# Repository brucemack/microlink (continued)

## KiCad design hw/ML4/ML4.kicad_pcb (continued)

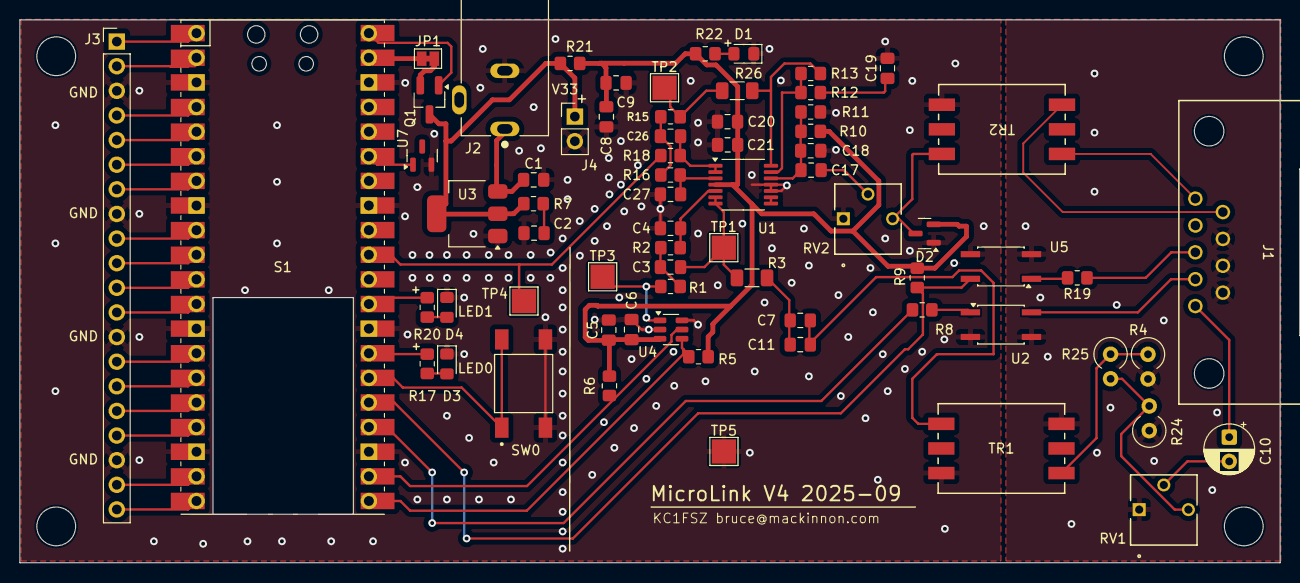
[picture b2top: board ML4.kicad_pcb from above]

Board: 2 copper layers, 130.0 x 56.0 mm, 73 parts (0 on the bottom side), 64 nets.

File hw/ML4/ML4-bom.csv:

"Reference","Value","LCSC","Datasheet","BOM Comments","Footprint","Qty","DNP","DK"
"C1,C2","22u","C45783","~","","Capacitor_SMD:C_0805_2012Metric_Pad1.18x1.45mm_HandSolder","2","",""
"C3,C26","22n","C1729","~","","Capacitor_SMD:C_0805_2012Metric_Pad1.18x1.45mm_HandSolder","2","",""
"C4,C27","10n","C1710 ","~","","Capacitor_SMD:C_0805_2012Metric_Pad1.18x1.45mm_HandSolder","2","",""
"C5,C7,C8,C9,C11,C17,C19,C20","47u","C16780 ","~","","Capacitor_SMD:C_0805_2012Metric_Pad1.18x1.45mm_HandSolder","8","",""
"C6,C18,C21","0.1u","C28233 ","~","","Capacitor_SMD:C_0805_2012Metric_Pad1.18x1.45mm_HandSolder","3","",""
"C10","47u (Optional DC Block)","C22320","~","","Capacitor_THT:CP_Radial_D5.0mm_P2.50mm","1","",""
"D2","BAT54S","C12765","https://www.diodes.com/assets/Datasheets/ds11005.pdf","","Package_TO_SOT_SMD:SOT-23","1","",""
"J1","DE9_Receptacle","C17515865","~","","bruce-footprints:CONN_A-DF 09 A&slash_KG-T2S_ASM","1","","AE10921-ND"
"J2","PJ-102AH","C3096093","","","bruce-footprints:Power_5.5mm_CUI_PJ-102AH","1","","CP-102AH-ND"
"J3","Conn_01x20","C22465880","~","Standard 2.54mm pin header","Connector_PinHeader_2.54mm:PinHeader_1x20_P2.54mm_Vertical","1","",""
"J4","Conn_01x02","C492401","~","Standard 2.54mm pin header","Connector_PinHeader_2.54mm:PinHeader_1x02_P2.54mm_Vertical","1","",""
"Q1","DMG2305UX-13","C144153","https://www.diodes.com/assets/Datasheets/DMG2305UX.pdf","","Package_TO_SOT_SMD:SOT-23_Handsoldering","1","",""
"R1,R15","1.5k","C4310","~","","Resistor_SMD:R_0805_2012Metric_Pad1.20x1.40mm_HandSolder","2","",""
"R2,R16","2.7k","C17530","~","","Resistor_SMD:R_0805_2012Metric_Pad1.20x1.40mm_HandSolder","2","",""
"R3,R18","0R","C17477","~","","Resistor_SMD:R_0805_2012Metric_Pad1.20x1.40mm_HandSolder,Resistor_SMD:R_1206_3216Metric_Pad1.30x1.75mm_HandSolder","2","",""
"R4","620","C58633","~","","Resistor_THT:R_Axial_DIN0309_L9.0mm_D3.2mm_P2.54mm_Vertical","1","",""
"R5,R6,R12,R13","2.2k","C17520","~","","Resistor_SMD:R_0805_2012Metric_Pad1.20x1.40mm_HandSolder","4","",""
"R7","10","C17415","~","","Resistor_SMD:R_0805_2012Metric_Pad1.20x1.40mm_HandSolder","1","",""
"R8,R19","220","C17557","~","","Resistor_SMD:R_0805_2012Metric_Pad1.20x1.40mm_HandSolder","2","",""
"R9","1k","C17513","~","","Resistor_SMD:R_0805_2012Metric_Pad1.20x1.40mm_HandSolder","1","",""
"R10","330k 1%","C17629","~","","Resistor_SMD:R_0805_2012Metric_Pad1.20x1.40mm_HandSolder","1","",""
"R11","270k 1%","C17589","~","","Resistor_SMD:R_0805_2012Metric_Pad1.20x1.40mm_HandSolder","1","",""
"R17,R20,R22","100","C17408","~","","Resistor_SMD:R_0805_2012Metric_Pad1.20x1.40mm_HandSolder","3","",""
"R21","4.7","C17675","~","","Resistor_SMD:R_0805_2012Metric_Pad1.20x1.40mm_HandSolder","1","",""
"R24","2,.2k","C58595 ","~","","Resistor_THT:R_Axial_DIN0309_L9.0mm_D3.2mm_P2.54mm_Vertical","1","",""
"R25","39k","C58645","~","","Resistor_THT:R_Axial_DIN0309_L9.0mm_D3.2mm_P2.54mm_Vertical","1","",""
"R26","0R 1206","C17888","~","","Resistor_SMD:R_1206_3216Metric_Pad1.30x1.75mm_HandSolder","1","",""
"RV1,RV2","50k","C81264","~","","bruce-footprints:POT_3362P","2","",""
"S1","~","C7203003","","","bruce-footprints:RPi_PicoW_SMD_TH","1","",""
"SW0","TS04-66-55-BK-160-SMT","C4364775","","","bruce-footprints:SW_TS04-66-55-BK-160-SMT","1","",""
"TR1,TR2","SM-LP-5001","C7503474","https://www.bourns.com/docs/Product-Datasheets/SMLP5001.pdf","","bruce-footprints:TRAN6_SM-LP-5001_BRN","2","",""
"U1","TLV9164PWR","C4368361","http://www.ti.com/lit/ds/symlink/lmv324.pdf","","Package_SO:TSSOP-14_4.4x5mm_P0.65mm","1","",""
"U2,U5","LTV-356T","C125117 ","http://optoelectronics.liteon.com/upload/download/DS70-2001-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","","Package_SO:SO-4_4.4x3.6mm_P2.54mm","2","",""
"U3","LM1117MP-3.3","C9662","http://www.ti.com/lit/ds/symlink/lm1117.pdf","","Package_TO_SOT_SMD:SOT-223-3_TabPin2","1","",""
"U4","MCP4725A0T-E/CH","C144198","http://ww1.microchip.com/downloads/en/DeviceDoc/22039d.pdf","","Package_TO_SOT_SMD:SOT-23-6","1","",""
"U7","LM4040D30IDBZR","C2157213","http://www.ti.com/lit/ds/symlink/lm4040-n.pdf","","Package_TO_SOT_SMD:SOT-23","1","",""
"D1","Red","C84256","~","","LED_SMD:LED_0805_2012Metric_Pad1.15x1.40mm_HandSolder","1","",""
"D3","Blue","C84259 ","~","","LED_SMD:LED_0805_2012Metric_Pad1.15x1.40mm_HandSolder","1","",""
"D4","Green","C2297","~","","LED_SMD:LED_0805_2012Metric_Pad1.15x1.40mm_HandSolder","1","",""

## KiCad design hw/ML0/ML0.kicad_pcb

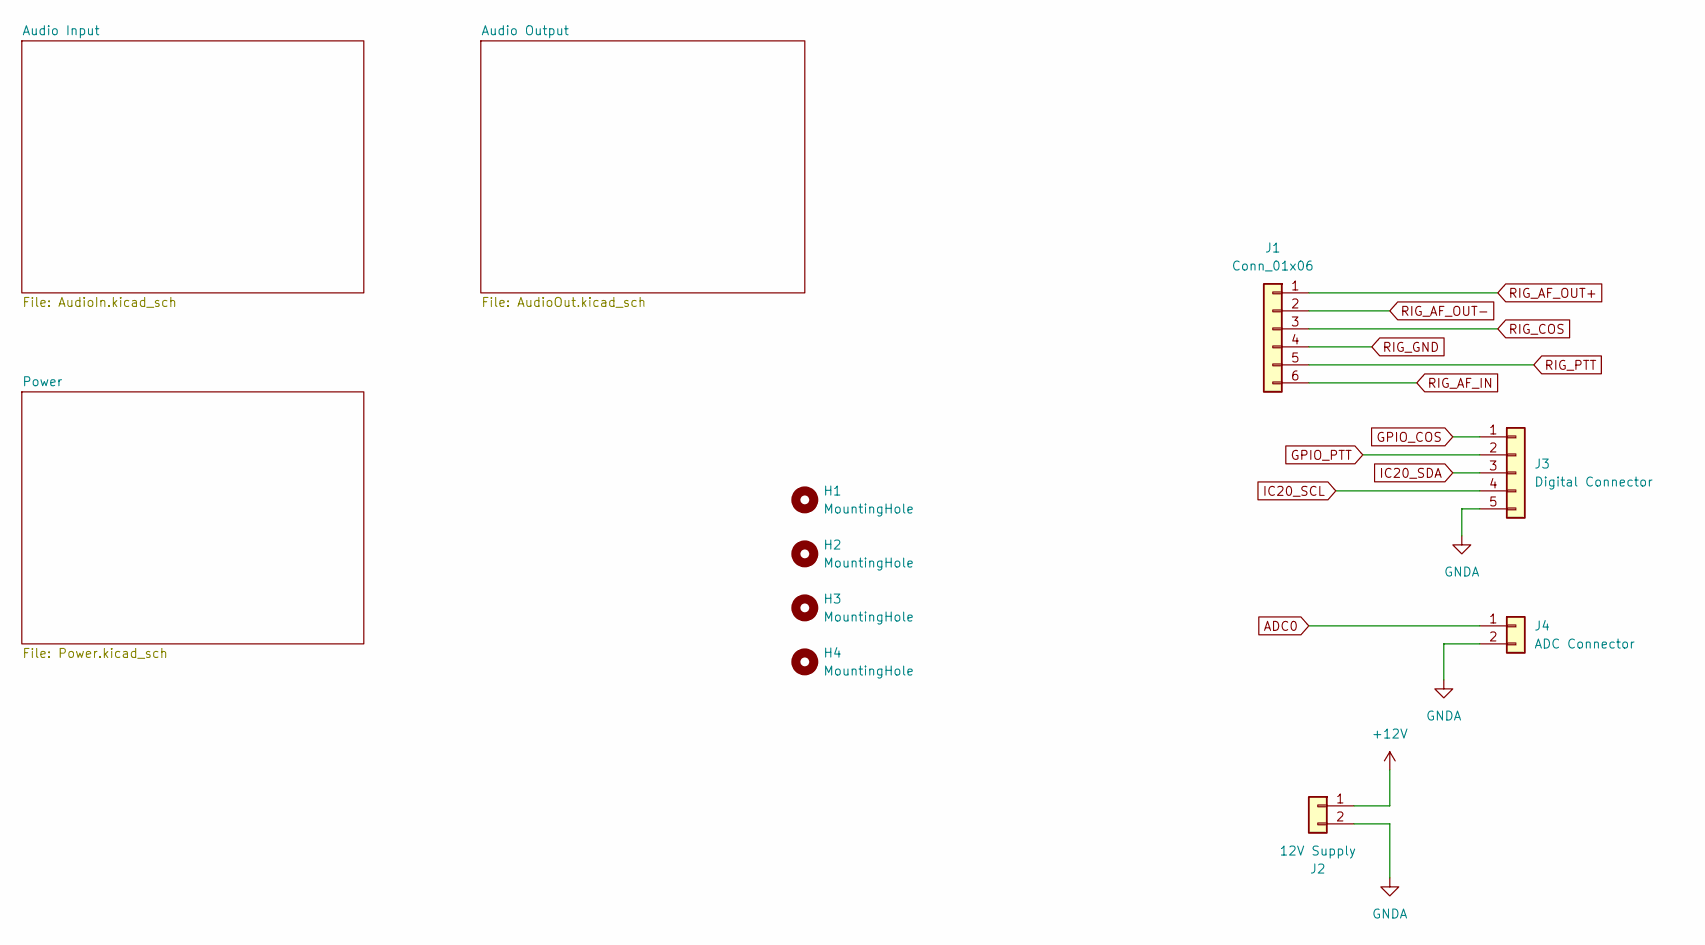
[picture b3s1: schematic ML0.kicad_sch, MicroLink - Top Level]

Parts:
H1, H2, H3, H4: MountingHole; MountingHole_4mm
J1: Conn_01x06; PinHeader_1x06_P2.54mm_Vertical
J2: 12V Supply; PinHeader_1x02_P2.54mm_Vertical
J3: Digital Connector; PinHeader_1x05_P2.54mm_Vertical
J4: ADC Connector; PinHeader_1x02_P2.54mm_Vertical

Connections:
+12V: J2.1; also elsewhere on the board
ADC0: J4.1; also elsewhere on the board
GNDA: J2.2, J3.5, J4.2; also elsewhere on the board
GPIO_COS: J3.1; also elsewhere on the board
GPIO_PTT: J3.2; also elsewhere on the board
IC20_SCL: J3.4; also elsewhere on the board
IC20_SDA: J3.3; also elsewhere on the board
RIG_AF_IN: J1.6; also elsewhere on the board
RIG_AF_OUT+: J1.1; also elsewhere on the board
RIG_AF_OUT-: J1.2; also elsewhere on the board
RIG_COS: J1.3; also elsewhere on the board
RIG_GND: J1.4; also elsewhere on the board
RIG_PTT: J1.5; also elsewhere on the board

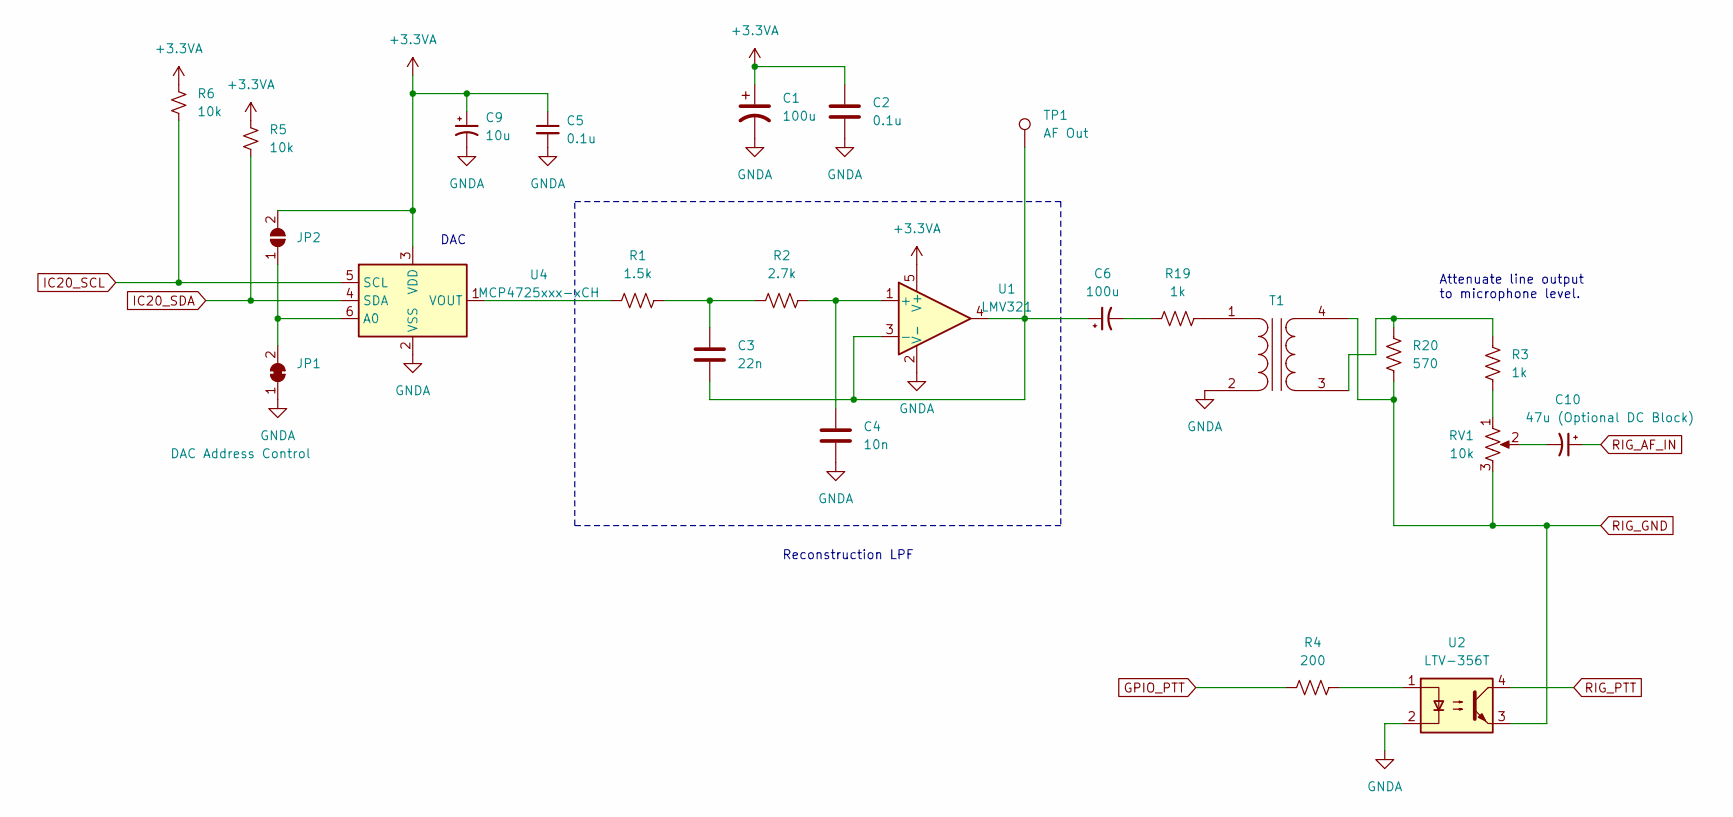
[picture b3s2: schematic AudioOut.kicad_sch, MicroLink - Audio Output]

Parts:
C1, C6: 100u; CAP_KEMET_530_530
C2, C5: 0.1u; C_0805_2012Metric_Pad1.18x1.45mm_HandSolder
C3: 22n; C_0805_2012Metric_Pad1.18x1.45mm_HandSolder
C4: 10n; C_0805_2012Metric_Pad1.18x1.45mm_HandSolder
C9: 10u; CAP_KEMET_530_530
C10: 47u (Optional DC Block); CP_Radial_D5.0mm_P2.50mm
JP1: DAC Address Control; SolderJumper-2_P1.3mm_Bridged_Pad1.0x1.5mm
JP2: SolderJumper_2_Open; SolderJumper-2_P1.3mm_Open_Pad1.0x1.5mm
R1: 1.5k; R_0805_2012Metric_Pad1.20x1.40mm_HandSolder
R2: 2.7k; R_0805_2012Metric_Pad1.20x1.40mm_HandSolder
R3, R19: 1k; R_0805_2012Metric_Pad1.20x1.40mm_HandSolder
R4: 200; R_0805_2012Metric_Pad1.20x1.40mm_HandSolder
R5, R6: 10k; R_0805_2012Metric_Pad1.20x1.40mm_HandSolder
R20: 570; R_0805_2012Metric_Pad1.20x1.40mm_HandSolder
RV1: 10k; POT_3362P
T1: Transformer_1P_1S; CheapAudioTransformer
TP1: AF Out; TestPoint_Pad_2.5x2.5mm
U1: LMV321; SOT-23-5_HandSoldering
U2: LTV-356T; SO-4_4.4x3.6mm_P2.54mm
U4: MCP4725xxx-xCH; SOT-23-6

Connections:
+3.3VA: C1.1, C2.1, C5.1, C9.1, JP2.2 (B), R5.1, R6.1, U1.5 (V+), U4.3 (VDD); also elsewhere on the board
GNDA: C1.2, C2.2, C4.2, C5.2, C9.2, JP1.1 (A), T1.2 (AB), U1.2 (V-), U2.2, U4.2 (VSS); also elsewhere on the board
GPIO_PTT: R4.1; also elsewhere on the board
IC20_SCL: R6.2, U4.5 (SCL); also elsewhere on the board
IC20_SDA: R5.2, U4.4 (SDA); also elsewhere on the board
unnamed: C3.1, R1.1, R2.1
unnamed: C6.2, R19.1
unnamed: C10.2, RV1.2
unnamed: JP1.2 (B), JP2.1 (A), U4.6 (A0)
unnamed: R3.2, RV1.1
unnamed: R4.2, U2.1
unnamed: R19.2, T1.1 (AA)
unnamed: R3.1, R20.1, T1.3 (SA)
unnamed: C4.1, R2.2, U1.1 (+)
unnamed: C3.2, C6.1, TP1.1, U1.3 (-), U1.4
unnamed: R1.2, U4.1 (VOUT)
RIG_AF_IN: C10.1; also elsewhere on the board
RIG_GND: R20.2, RV1.3, T1.4 (SB), U2.3; also elsewhere on the board
RIG_PTT: U2.4; also elsewhere on the board

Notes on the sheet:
Reconstruction LPF
Attenuate line output to microphone level.
DAC

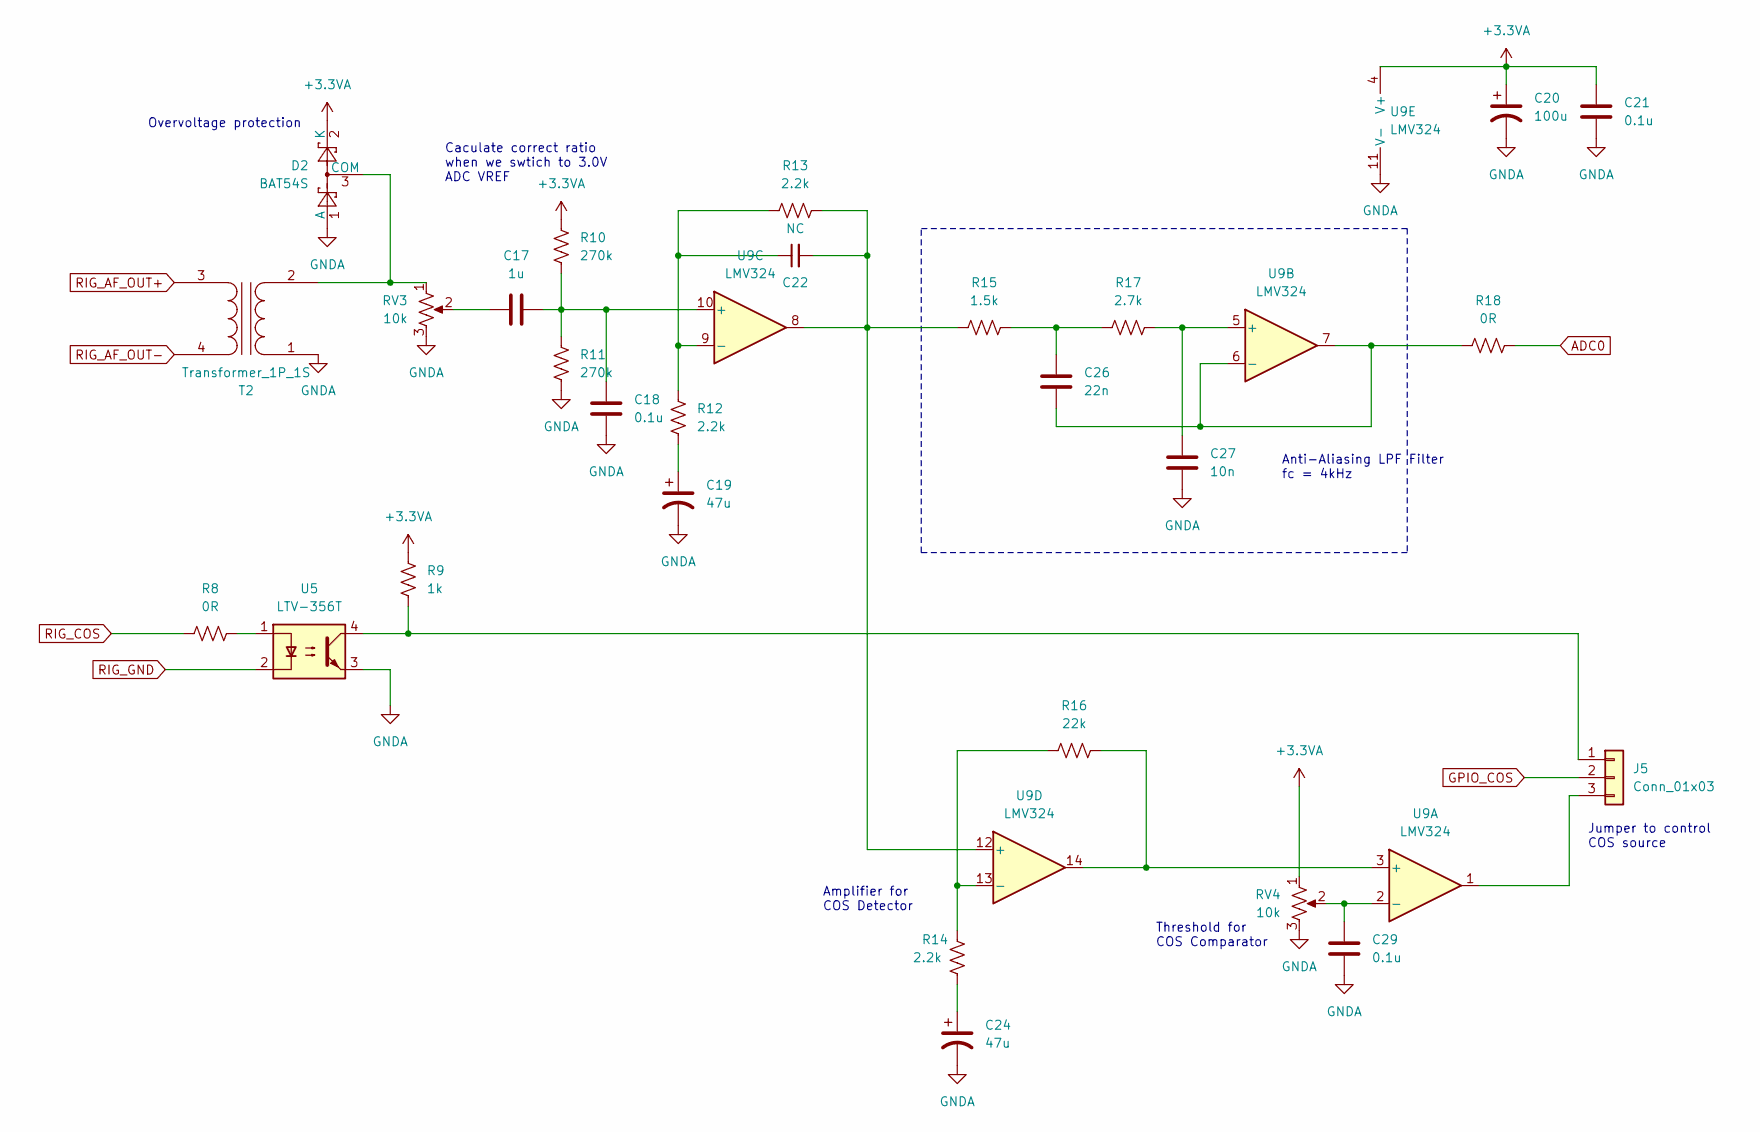
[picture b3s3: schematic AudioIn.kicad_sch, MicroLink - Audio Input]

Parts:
C17: 1u; C_0805_2012Metric_Pad1.18x1.45mm_HandSolder
C18, C21, C29: 0.1u; C_0805_2012Metric_Pad1.18x1.45mm_HandSolder
C19, C24: 47u; CAP_KEMET_530_530
C20: 100u; CAP_KEMET_530_530
C22: NC; C_0805_2012Metric_Pad1.18x1.45mm_HandSolder
C26: 22n; C_0805_2012Metric_Pad1.18x1.45mm_HandSolder
C27: 10n; C_0805_2012Metric_Pad1.18x1.45mm_HandSolder
D2: BAT54S; SOT-23
J5: Conn_01x03; PinHeader_1x03_P2.54mm_Vertical
R8, R18: 0R; R_0805_2012Metric_Pad1.20x1.40mm_HandSolder
R9: 1k; R_0805_2012Metric_Pad1.20x1.40mm_HandSolder
R10, R11: 270k; R_0805_2012Metric_Pad1.20x1.40mm_HandSolder
R12, R13, R14: 2.2k; R_0805_2012Metric_Pad1.20x1.40mm_HandSolder
R15: 1.5k; R_0805_2012Metric_Pad1.20x1.40mm_HandSolder
R16: 22k; R_0805_2012Metric_Pad1.20x1.40mm_HandSolder
R17: 2.7k; R_0805_2012Metric_Pad1.20x1.40mm_HandSolder
RV3, RV4: 10k; POT_3362P
T2: Transformer_1P_1S; CheapAudioTransformer
U5: LTV-356T; SO-4_4.4x3.6mm_P2.54mm
U9: LMV324; TSSOP-14_4.4x5mm_P0.65mm

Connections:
+3.3VA: C20.1, C21.1, D2.2 (K), R9.1, R10.1, RV4.1, U9.4 (V+); also elsewhere on the board
ADC0: R18.2; also elsewhere on the board
GNDA: C18.2, C19.2, C20.2, C21.2, C24.2, C27.2, C29.2, D2.1 (A), R11.2, RV3.3, RV4.3, T2.1 (AA), U5.3, U9.11 (V-); also elsewhere on the board
GPIO_COS: J5.2; also elsewhere on the board
unnamed: C17.1, RV3.2
unnamed: C19.1, R12.1
unnamed: C24.1, R14.1
unnamed: C26.1, R15.1, R17.1
unnamed: D2.3 (COM), RV3.1, T2.2 (AB)
unnamed: J5.1, R9.2, U5.4
unnamed: J5.3, U9.1
unnamed: R8.2, U5.1
unnamed: R16.2, U9.3 (+), U9.14
unnamed: C29.1, RV4.2, U9.2 (-)
unnamed: C27.1, R17.2, U9.5 (+)
unnamed: C26.2, R18.1, U9.6 (-), U9.7
unnamed: C17.2, C18.1, R10.2, R11.1, U9.10 (+)
unnamed: C22.1, R12.2, R13.1, U9.9 (-)
unnamed: C22.2, R13.2, R15.2, U9.8, U9.12 (+)
unnamed: R14.2, R16.1, U9.13 (-)
RIG_AF_OUT+: T2.3 (SA); also elsewhere on the board
RIG_AF_OUT-: T2.4 (SB); also elsewhere on the board
RIG_COS: R8.1; also elsewhere on the board
RIG_GND: U5.2; also elsewhere on the board

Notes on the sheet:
Overvoltage protection
Amplifier for COS Detector
Threshold for COS Comparator
Jumper to control COS source
Anti-Aliasing LPF Filter fc = 4kHz
Caculate correct ratio when we swtich to 3.0V ADC VREF

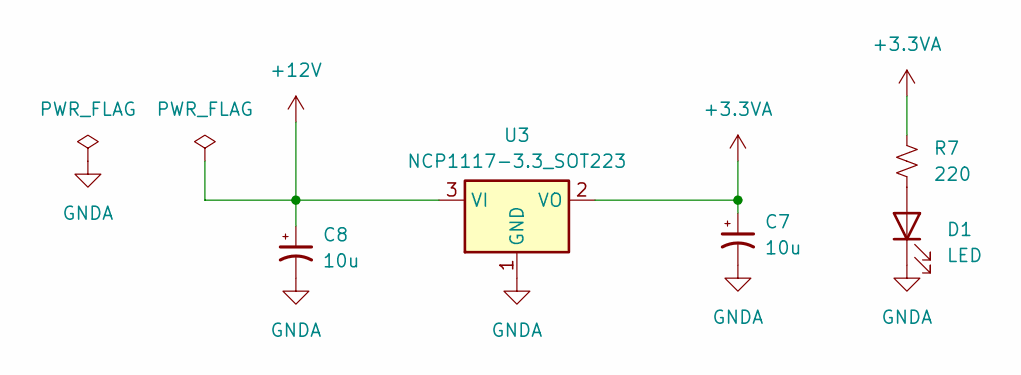
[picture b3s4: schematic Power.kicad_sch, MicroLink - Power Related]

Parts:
C7, C8: 10u; CAP_KEMET_530_530
D1: LED; LED_0805_2012Metric_Pad1.15x1.40mm_HandSolder
R7: 220; R_0805_2012Metric_Pad1.20x1.40mm_HandSolder
U3: NCP1117-3.3_SOT223; SOT-223-3_TabPin2

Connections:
+3.3VA: C7.1, R7.1, U3.2 (VO); also elsewhere on the board
+12V: C8.1, U3.3 (VI); also elsewhere on the board
GNDA: C7.2, C8.2, D1.1 (K), U3.1 (GND); also elsewhere on the board
unnamed: D1.2 (A), R7.2

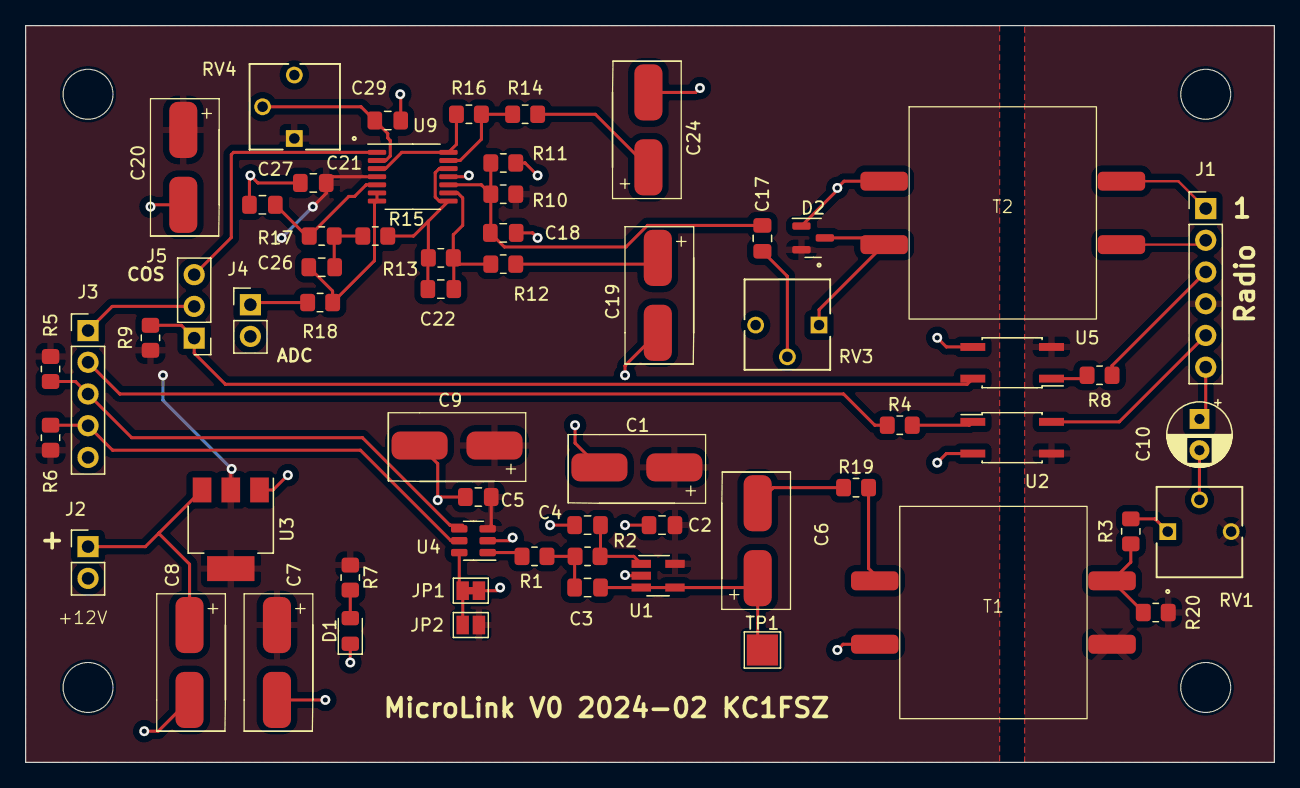
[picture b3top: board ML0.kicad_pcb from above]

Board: 2 copper layers, 100.0 x 59.0 mm, 65 parts (0 on the bottom side), 42 nets.

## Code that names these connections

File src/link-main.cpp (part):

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// ===============

// Phy Pin 21: I2C channel 0 - DAC data
#define I2C0_SDA (16) 
// Phy Pin 22: I2C channel 0 - DAC clock
#define I2C0_SCL (17) 

// Physical pin 23 - GROUND

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#define RIG_KEY_PIN (18)
// Physical pin 25. This is an input (active high) used to detect
// receive carrier from the rig. 
#define RIG_COS_PIN (19)

// No physical pin on board
//#define LED_PIN (25)
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    gpio_set_dir(PTT_PIN, GPIO_IN);
    gpio_pull_up(PTT_PIN);

    gpio_init(RIG_COS_PIN);
    gpio_set_dir(RIG_COS_PIN, GPIO_IN);
    gpio_pull_up(RIG_COS_PIN);

    // Key/indicator LED
    gpio_init(KEY_LED_PIN);
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
    // Setup I2C
    i2c_init(i2c_default, 100 * 1000);
    gpio_set_function(I2C0_SDA, GPIO_FUNC_I2C);
    gpio_set_function(I2C0_SCL, GPIO_FUNC_I2C);
    gpio_pull_up(I2C0_SDA);
    gpio_pull_up(I2C0_SCL);
    //i2c_set_baudrate(i2c_default, 400000 * 4);
    i2c_set_baudrate(i2c_default, 800000);

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        // 2. Soft COS: thresholding noise level on receiver

        bool rigCos = (useHardCos) ? 
            gpio_get(RIG_COS_PIN) : (rxAnalyzer.getRMS() - baselineRxNoise) > (int16_t)rxNoiseThreshold;

        // Produce a debounced cosState, whcih indicates the state of
        // the carrier detect.
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
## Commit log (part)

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2024-01-25 Added example of ONLINE packet
2024-01-25 Centralized the version ID
2024-01-25 Working on directory request
2024-01-25 Server lookup
2024-01-26 Asterisk reference
2024-01-26 Testing on PICO
2024-01-26 Working on cross-platform
2024-01-26 State machine work in process
2024-01-28 Updates from server test
2024-01-28 Cleaned typos
2024-01-28 Working on state machine
2024-01-28 Added more message types
2024-01-28 State machine work
2024-01-28 State machine is working
2024-01-29 Working on socket context
2024-01-29 SocketContext is starting to work, new client test
2024-01-29 Logon/Lookup is working properly on the real EchoLink
2024-01-29 Corrected directory errors
2024-01-29 Switched to NL order on IP address
2024-01-29 UDP working in SocketContext
2024-01-29 Cleaned up oNDATA problem
2024-01-30 Working on audio chain
2024-01-30 W32AudioOutputContext working
2024-01-30 Full receive station working with ECHOTEST
2024-01-30 Cleaned up some test cases
2024-01-30 Refactoring modules
2024-01-30 Cleaning up structure
2024-01-30 Refactoring tools repo
2024-01-30 Moving common files
2024-01-31 Receive test on *ECHOTEST* is working!
2024-01-31 Added some ESP32 stuff
2024-01-31 Working on audio glitch
2024-01-31 Added test case for talking to ESP32 AT commands
2024-02-01 Timing work
2024-02-01 Debugging interupt problems
2024-02-01 Refactored and move things to tools
2024-02-01 Refactoring AT code
2024-02-03 Making improvements to the ATProcessor - more async
2024-02-03 Streamlined AT matcher
2024-02-03 Addressed some AT parsing problems
2024-02-03 added #,CONNECT
2024-02-03 Added support for +CIPDOMAIN
2024-02-03 Starting to integrate EventProcesspr
2024-02-03 Updated state machine
2024-02-03 Working on PI-based EL client
2024-02-04 Initial connection test
2024-02-05 Working on directory lookup
2024-02-05 New lookup working (Verify mode)
2024-02-05 Added information about Extended Verify from K1RFD
2024-02-05 client test 2p
2024-02-05 Connect working!
2024-02-06 Working on initial reset
2024-02-06 Able to maintain sustained QSO with *ECHOTEST*
2024-02-07 Receive audio path is working
2024-02-07 EL receiver is working
2024-02-07 Added jitter-elimination
2024-02-07 Documentation
2024-02-07 Docs
2024-02-07 Cleaning up test cases
2024-02-07 Added information on pacing
2024-02-07 Adding input audio
2024-02-08 Refactoring QSOFlowMachine to support TX (NOT TESTED)
2024-02-08 Refactored SocketContext for Windows, now working on Windows (ECHOTEST)
2024-02-08 Heard an initial test tone back from ECHOTEST, but not fully working
2024-02-08 TX working consistently
2024-02-08 Able to TX a tone and hear it back on *ECHOTEST*
2024-02-08 Adding microphone hardward
2024-02-08 Working on microphone integration
2024-02-08 Seeing ADC queue add fails
2024-02-09 Refactor of ADC code (not tested yet)
2024-02-09 Tone TX working well now
2024-02-09 Successful test with TX and TX!
2024-02-11 Working on fixing deadlock in UART TX path - NOT TESTED
2024-02-11 New TX method tested successfully
2024-02-11 New tone scheme
2024-02-12 Refactoring to include Runnable interface, added timing stuff
2024-02-12 Now enabling ADC for TX only, tested
2024-02-12 Added beep on unsquelch
2024-02-12 Added ability to close a QSO cleanly
2024-02-12 Added model for preamp
2024-02-12 Working on remote linking test case - able to accept UDP traffic
2024-02-13 Added references
2024-02-13 Centering audio on silence
2024-02-13 Schematic updates
2024-02-13 Created test sdes file
2024-02-13 Fixed SDES bug - not tested
2024-02-13 SDES parsing test
2024-02-13 Link station work
2024-02-14 Successful test of W1TKZ-L
2024-02-14 Merged
2024-02-14 Doc improvements
2024-02-14 Removed lock on RX path
2024-02-15 Over the air testing is working
2024-02-16 Working on completing the state machine for linking (NOT TESTED)
2024-02-17 Added BYE support (Not Tested)
2024-02-17 Added timeout for long transmissions, now ignoring inbound traffic from non-accepted peers
2024-02-18 Working on PCB layout
2024-02-18 Link station test passed (on air)!
2024-02-19 Working on voice prompts
2024-02-19 Updating handling of silence
2024-02-19 Prompts working better
2024-02-19 Lowered volume on prompts
2024-02-19 This version of the code had a live QSO with W1DAN and WA1UMU on the WAES repeater.
2024-02-19 Corrected a defect which caused timeout during long TX
2024-02-19 Working on DAC timing
2024-02-20 Docs update
2024-02-20 Working on V0 of the analog PCB
2024-02-20 Adding description of challenge/response login
2024-02-20 Added docs on Login
2024-02-20 Making an offcial station main
2024-02-20 Cleaned up build
2024-02-20 Working on PCB 0
2024-02-21 Updates to docs
2024-02-21 Refactored RX path to enable DTMF in the future. Skipping Welcome after recent activity
2024-02-22 Adding TX audio
2024-02-23 Working on improvements to the audio out
2024-02-24 Refactored _state management. Changed audio output to be driven by ADC clock. (NOT TESTED)
2024-02-24 Working on new DAC scheme
2024-02-24 Now using analytical tone generation instead of lookup table
2024-02-25 Added audio analyzer on TX
2024-02-25 Initial layout done
2024-02-25 Working on PCB
2024-02-26 Improvements to board
2024-02-26 Board sent to JLC on 2024-02-26 09:18 EST
2024-02-26 DTMF detector is working
2024-02-27 Working on debug of audio glitches
2024-02-27 Moved configuration information into flash - no more hard-coding callsign/password
2024-02-27 Improved logging
2024-02-27 Improving logging
2024-02-27 Integrated serial log for OpenLog hardware
2024-02-27 Serial logging working now
2024-02-28 Working on DTMF
2024-02-29 Improved COS handling
2024-02-29 First board
2024-02-29 DTMF test case workig
2024-02-29 DTMF test passing (mostly)
2024-03-04 Working on Pico W integration
2024-03-05 Removed panic, added assignment operator to Channel
2024-03-05 Tested successfully on Pico W
2024-03-05 Working on multi-user conference (not tested)
2024-03-06 Preliminary push of conference-enabled link (NOT TESTED)
2024-03-06 LogonMachine2 is working
2024-03-06 ConferenceBridge added
2024-03-06 Conference authorization is working
2024-03-06 ECHOTEST successful via conference
2024-03-06 Physical radio TX path tested
2024-03-07 Full system (w/ radio) working again
2024-03-07 Added a few other kbd commands
2024-03-07 More testing, improved LED indicators and timeouts
2024-03-07 Removed a lot of obsolete files - moving on to Conference (TESTED ON AIR)
2024-03-07 Cleaned out unused files
2024-03-07 Avoiding logon before link comes up
2024-03-07 Added monitor. needed to incrase UDP socket count
2024-03-08 Now pinging the Addressing Server
2024-03-08 Working on OPEN/OVER - not working yet
2024-03-09 System tested with V0 board
2024-03-09 Working on docs: OPEN/OVER
2024-03-09 V0 board has been tested
2024-03-09 Addressed a bug that caused session to drop during long transmission
2024-03-09 Working on monitor
2024-03-10 Micro-optimizations
2024-03-10 Changed RMS to MS on RX threshold detection to eliminate sqrt(), streamlined some audio paths. Tested on the air
2024-03-10 Attemping to address contention between GSM decoding (for radio) and forwarding packets to other nodes. Also enabled monitor key control
2024-03-10 Removed dead file
2024-03-17 Working on chat
2024-03-19 New files for SIM7600
2024-03-19 Working on SIM7600, moved back to WIFI for testing. Made a change to the DC bias calculation to remove COS problem
2024-03-20 Working on SIM7600
2024-03-20 Fixed DC offset
2024-03-22 Working on docs
2024-03-25 Added power pin for SIM7600
2024-03-27 Working well, added diagnostics, improved station limit case
2024-03-28 Working on ML1
2024-03-28 Working:
2024-03-28 Re-work of ML1 board in process
2024-03-28 First draft of board is passing DRC
2024-03-28 Final checks, preparing to create GRB
2024-03-29 Added sanity check
2024-03-30 SIM7600 cellular link starting to work!
2024-04-01 Able to logon as *ANALYZER*
2024-04-01 Cellular connection working well!
2024-04-01 Documentation for cellular option
2024-04-01 Merging development work
2024-04-02 Added official BOM
2024-04-04 Commiting SIM7600 code and switching back to WIFI
2024-04-04 Working again on WIFI (adjusted bind protocol)
2024-04-09 Working on ML1 bring-up
2024-04-09 Changed audio power calculation
2024-04-09 Added command shell
2024-04-09 Major refactor of timestamps, Runnable
2024-04-10 Added retry on validation to resolve a connect problem
2024-04-10 PCB layout changes
2024-04-10 Board passing checks, ready for review
2024-04-10 Plot files generated for fab
2024-04-10 Updated BOM
2024-04-11 Merged dev
2024-04-11 Added NTP time synchronization, improved logging
2024-04-12 Cleaned up logging
2024-04-12 NTP Docs
2024-04-14 Working on packaging for ML3
2024-04-15 ML3 board modified for improved case/DFM. Sending this version to Steve
2024-04-16 Added documentation about isolation - no board changes
2024-04-17 Added 3d models
2024-04-17 V3 R1 incorporating connector moves from Steve
2024-04-20 Latest docs
2024-04-23 Class naming cleanup
2024-04-26 V3 pictures
2024-04-26 Updates for ML4
2024-04-27 V3 assembly
2024-04-27 Pictures
2024-10-24 Adding new rig information
2024-10-24 Adding DB9 pinout
2024-11-01 Fixed pinout error
2025-01-20 Fixed doc typos
2025-01-20 Added pic
2025-01-20 Updated photo
2025-09-25 Working on JCSC BOM
2025-09-30 Working on adding LCSC part numbers
2025-10-01 Working on ML4
2025-10-02 Cleaned up some build problems
2025-10-06 Added factoryreset, cleaned u p prompts
2025-10-06 Added breakout board for SA818 module
2025-10-07 Updating PCB
2025-10-07 Added LPF for harmonics
2025-10-07 SA818 stuff
2025-10-08 Adding test case for AllStarLink
2025-10-09 Updated 50ohm traces
2025-10-09 Working on manual RSA authentication
2025-10-11 Working on mp
2025-10-11 Working on div
2025-10-11 Simple div working
2025-10-20 Narrowing interface
2025-10-20 AllStarLink docs
2025-10-21 Working on Python implementation of a hub note
2025-10-21 Working on Python implementation of a hub node
2025-10-21 Call setup is working
2025-10-21 Basic server working, but audio is choppy on Windows
2025-10-21 Working well, audio is smooth now
2025-10-21 Cleanup, comments
2025-10-21 Moved files out
2025-10-22 New test case for SIP validation
2025-10-28 More IAX docs
2025-10-28 Added some traces for R&D
2025-10-28 Working on ML2
2025-10-28 Moved ASL files out to new repo
